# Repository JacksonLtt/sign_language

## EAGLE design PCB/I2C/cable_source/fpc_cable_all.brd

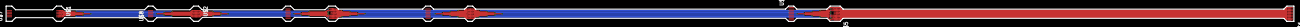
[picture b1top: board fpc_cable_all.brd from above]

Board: 2 copper layers, 422.3 x 5.0 mm, 11 parts (0 on the bottom side), 9 nets.

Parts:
U$1, U$2, U$7, U$8: FPC050505; FPC0505
U$3, U$4, U$9, U$10: FPC070505; FPC0705
U$5, U$6, U$11: FPC090505; FPC0905

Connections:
1.8V: U$1.P$4, U$2.P$4, U$3.P$5, U$4.P$5, U$5.P$6, U$6.P$6
GND: U$1.P$1, U$2.P$1, U$3.P$2, U$4.P$2, U$5.P$3, U$6.P$3
SCL1: U$5.P$4, U$6.P$4
SCL2: U$3.P$3, U$4.P$3, U$5.P$2, U$6.P$2
SCL3: U$1.P$2, U$2.P$2, U$3.P$1, U$4.P$1, U$5.P$1, U$6.P$1
SDA1: U$5.P$5, U$6.P$5
SDA2: U$3.P$4, U$4.P$4, U$5.P$8, U$6.P$8
SDA3: U$1.P$3, U$2.P$3, U$3.P$7, U$4.P$7, U$5.P$9, U$6.P$9
VIN: U$1.P$5, U$2.P$5, U$3.P$6, U$4.P$6, U$5.P$7, U$6.P$7

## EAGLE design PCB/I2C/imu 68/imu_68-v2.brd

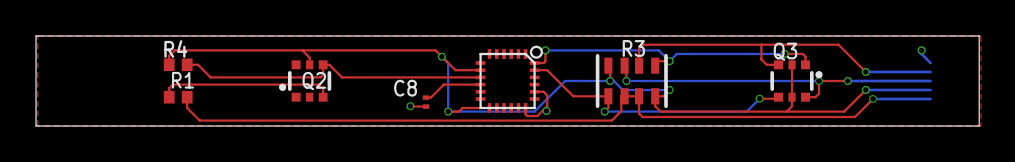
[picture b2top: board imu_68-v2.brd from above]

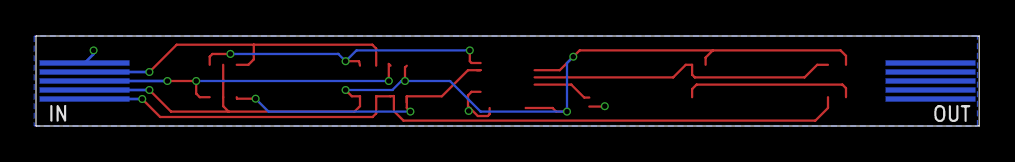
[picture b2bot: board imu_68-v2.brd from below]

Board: 2 copper layers, 52.4 x 5.0 mm, 9 parts (2 on the bottom side), 9 nets.

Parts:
C8: 0.1uF; C0201
Q2, Q3: BSS138; SOT363
R1, R4: 4.7k; R0402
R3: 10K; RESPACK_4X0603
U$1, U$2: FPC0510
U$21: MPU-9250_ICM20948; QFN24_3MM_NOEP

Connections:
1.8V: Q2.5, Q3.2, Q3.5, R3.4, R3.8, R4.2, U$1.P$2, U$21.8, U$21.13
GND: C8.2, Q2.3, R1.1, U$1.P$5, U$21.18, U$21.20
REGOUT: C8.1, U$21.10
SCK/SCL: Q3.3, R3.6, U$1.P$4
SCK/SCL_1.8V: Q3.4, R3.1, U$21.23
SDI/SDA: Q3.6, R3.7, U$1.P$3
SDI/SDA_1.8V: Q3.1, R3.5, U$21.24
SDO/ADR_1.8V: Q2.4, R4.1, U$21.9
VIN: R1.2, R3.2, R3.3, U$1.P$1

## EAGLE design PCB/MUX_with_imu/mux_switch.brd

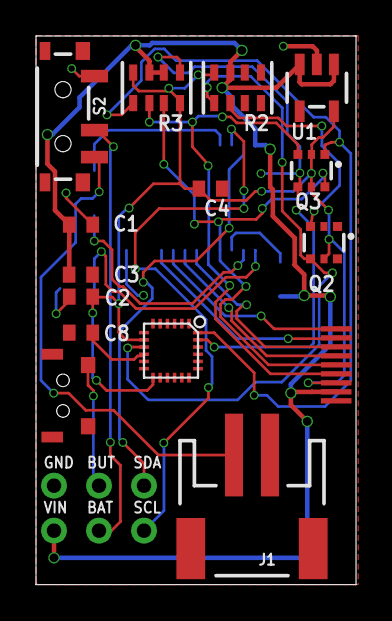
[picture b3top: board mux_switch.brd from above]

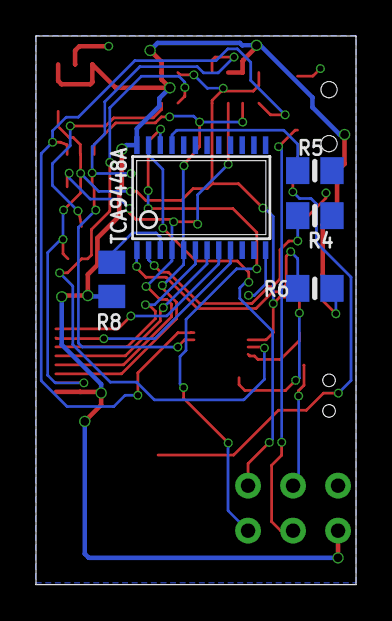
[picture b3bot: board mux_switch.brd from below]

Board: 2 copper layers, 17.8 x 30.5 mm, 26 parts (5 on the bottom side), 23 nets.

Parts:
C1: 1uF; C0402
C2: 2.2uF; C0402
C3: 10uF; C0402
C4, C8: 0.1uF; C0402
J1: JST-2-SMD
Q2, Q3: BSS138; SOT363
R2: 4.7K; RESPACK_4X0603
R3: 10K; RESPACK_4X0603
R4, R5, R6: 10K; 0805-NO
R8: 10k; R0805
S2: SWITCH_SPST_SMD_A
TCA9448A: MICROBUILDER_TSSOP24
U1: MIC5225-1.8V; SOT23-5
U$2: 24*3.5; 2*4*3.5
U$3, U$6, U$8, U$9, U$10, U$12: M0.9-HOLE0.9MM; M0.9-HOLE
U$13: FPC090505; FPC0905
U$21: MPU-9250_ICM20948; QFN24_3MM_NOEP

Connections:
1.8V: C2.1, C4.1, Q2.5, Q3.2, Q3.5, R2.8, R3.4, R3.8, U1.5, U$13.P$7, U$21.8, U$21.13
BATTERY: S2.2, U$10.P$1
BUTTON: U$2.P$4, U$9.P$1
GND: C1.2, C2.2, C3.2, C4.2, C8.2, J1.1, R4.2, R5.2, R6.2, S2.3, TCA9448A.12, U1.2, U$2.P$3, U$8.P$1, U$13.P$9, U$21.18, U$21.20
unnamed: R5.1, TCA9448A.21
unnamed: J1.2, S2.1
unnamed: R4.1, TCA9448A.2
unnamed: R6.1, TCA9448A.1
REGOUT: C8.1, U$21.10
RESET: R8.1, TCA9448A.3
SCK/SCL_1.8V: Q3.4, R3.1, U$21.23
SCL: TCA9448A.22, U$12.P$1
SCL1: Q3.3, R3.6, TCA9448A.5, U$13.P$6
SCL2: TCA9448A.7, U$13.P$4
SCL3: TCA9448A.9, U$13.P$2
SDA: TCA9448A.23, U$6.P$1
SDA1: Q3.6, R3.7, TCA9448A.4, U$13.P$5
SDA2: TCA9448A.6, U$13.P$3
SDA3: TCA9448A.8, U$13.P$1
SDI/SDA_1.8V: Q3.1, R3.5, U$21.24
SDO/ADR: Q2.3, R2.2
SDO/ADR_1.8V: Q2.4, R2.1, U$21.9
VIN: C1.1, C3.1, R2.7, R3.2, R3.3, R8.2, TCA9448A.24, U1.1, U1.3, U$3.P$1, U$13.P$8

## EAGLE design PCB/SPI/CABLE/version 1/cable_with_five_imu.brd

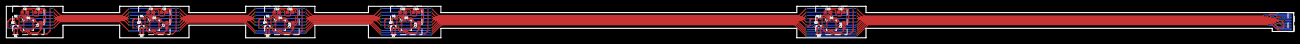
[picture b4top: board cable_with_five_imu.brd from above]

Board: 2 copper layers, 408.8 x 10.0 mm, 36 parts (1 on the bottom side), 21 nets.

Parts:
C4, C5, C7, C8, C10, C11, C13, C14, C16, C17: 0.1uF; 0603
C6, C9, C12, C15, C18: 1.0uF; 0603
Q1, Q3, Q4, Q5, Q6: 20V/0.2A/8MHz/1.2Ω/1Vth; SOT-416FL
R1, R2, R3, R4, R5, R6, R7, R8, R9, R12: 2.2k; 0402-TIGHT
U1, U3, U4, U5, U6: 9DoF IMU; QFN24-3X3
U$1: FPC1105

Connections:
1.8V: C5.1, C6.1, C8.1, C9.1, C11.1, C12.1, C14.1, C15.1, C17.1, C18.1, Q1.1, Q3.1, Q4.1, Q5.1, Q6.1, R1.2, R3.2, R5.2, R7.2, R9.2, U1.8, U1.13, U3.8, U3.13, U4.8, U4.13, U5.8, U5.13, U6.8, U6.13, U$1.P$5
!CS1: Q6.2, R9.1, U6.22
!CS2: Q5.2, R7.1, U5.22
!CS3: Q4.2, R5.1, U4.22
!CS4: Q3.2, R3.1, U3.22
!CS5: Q1.2, R1.1, U1.22
!CS!_VIN1: Q6.3, R12.1, U$1.P$8
!CS!_VIN2: Q5.3, R8.1, U$1.P$7
!CS!_VIN3: Q4.3, R6.1, U$1.P$6
!CS!_VIN4: Q3.3, R4.1, U$1.P$11
!CS!_VIN5: Q1.3, R2.1, U$1.P$10
GND: C4.2, C5.2, C6.2, C7.2, C8.2, C9.2, C10.2, C11.2, C12.2, C13.2, C14.2, C15.2, C16.2, C17.2, C18.2, U1.18, U1.20, U3.18, U3.20, U4.18, U4.20, U5.18, U5.20, U6.18, U6.20, U$1.P$1
MISO_VIN: U1.9, U3.9, U4.9, U5.9, U6.9, U$1.P$2
MOSI_VIN: U1.24, U3.24, U4.24, U5.24, U6.24, U$1.P$4
unnamed: C4.1, U1.10
unnamed: C7.1, U3.10
unnamed: C10.1, U4.10
unnamed: C13.1, U5.10
unnamed: C16.1, U6.10
SCLK_VIN: U1.23, U3.23, U4.23, U5.23, U6.23, U$1.P$3
VIN: R2.2, R4.2, R6.2, R8.2, R12.2, U$1.P$9

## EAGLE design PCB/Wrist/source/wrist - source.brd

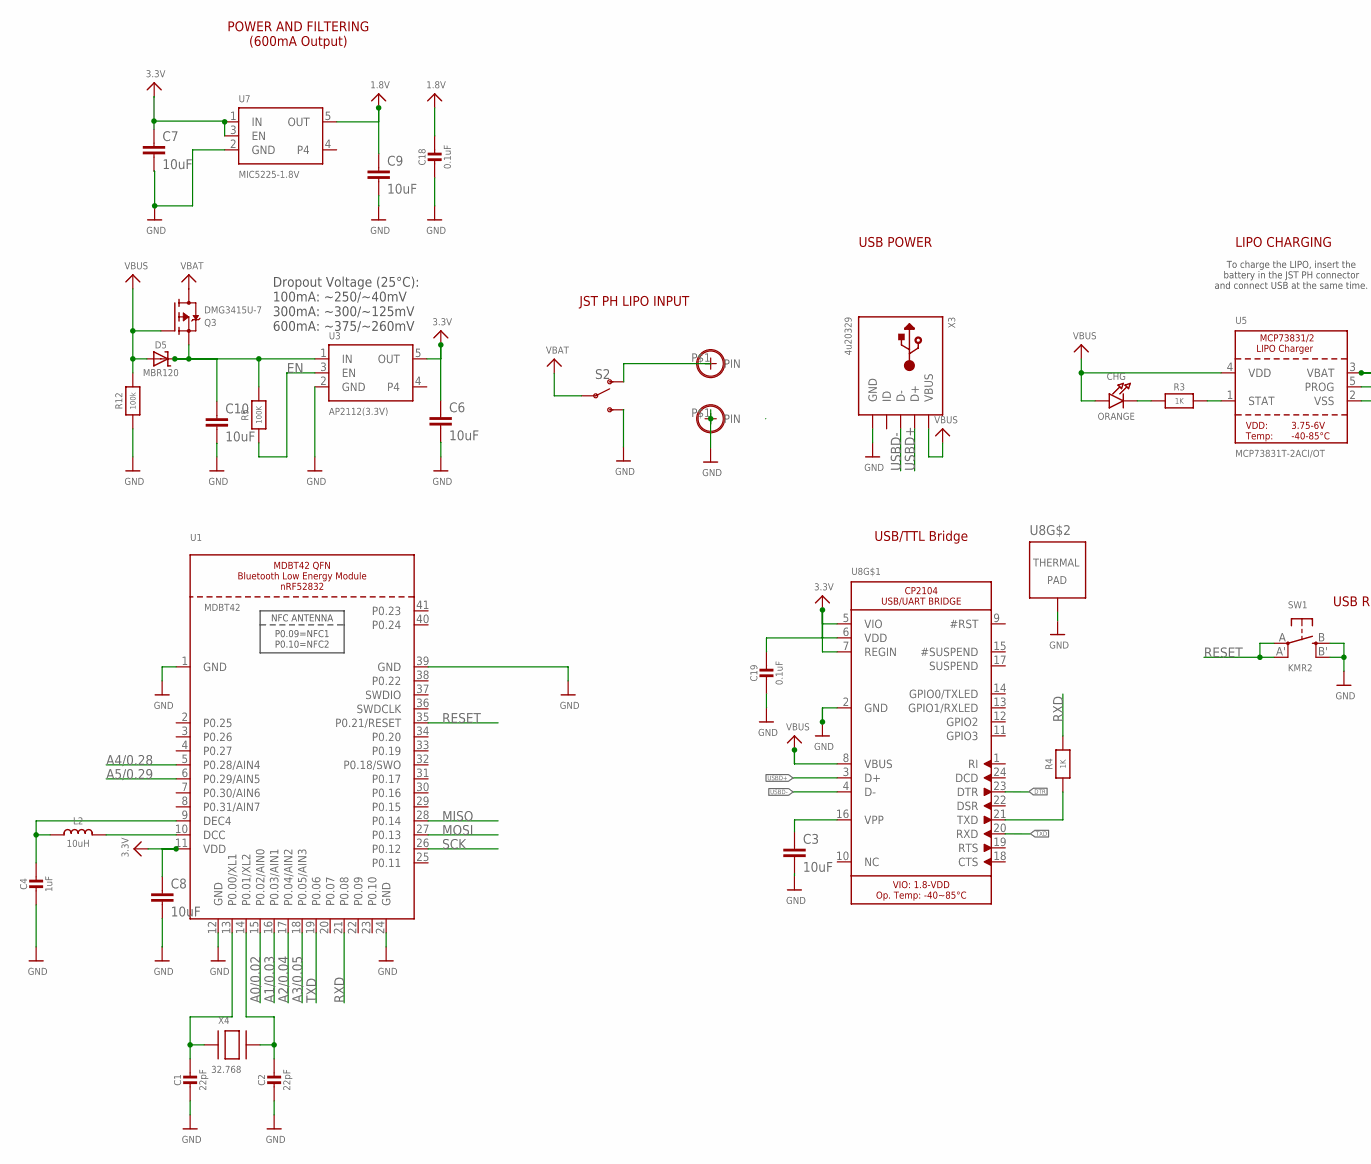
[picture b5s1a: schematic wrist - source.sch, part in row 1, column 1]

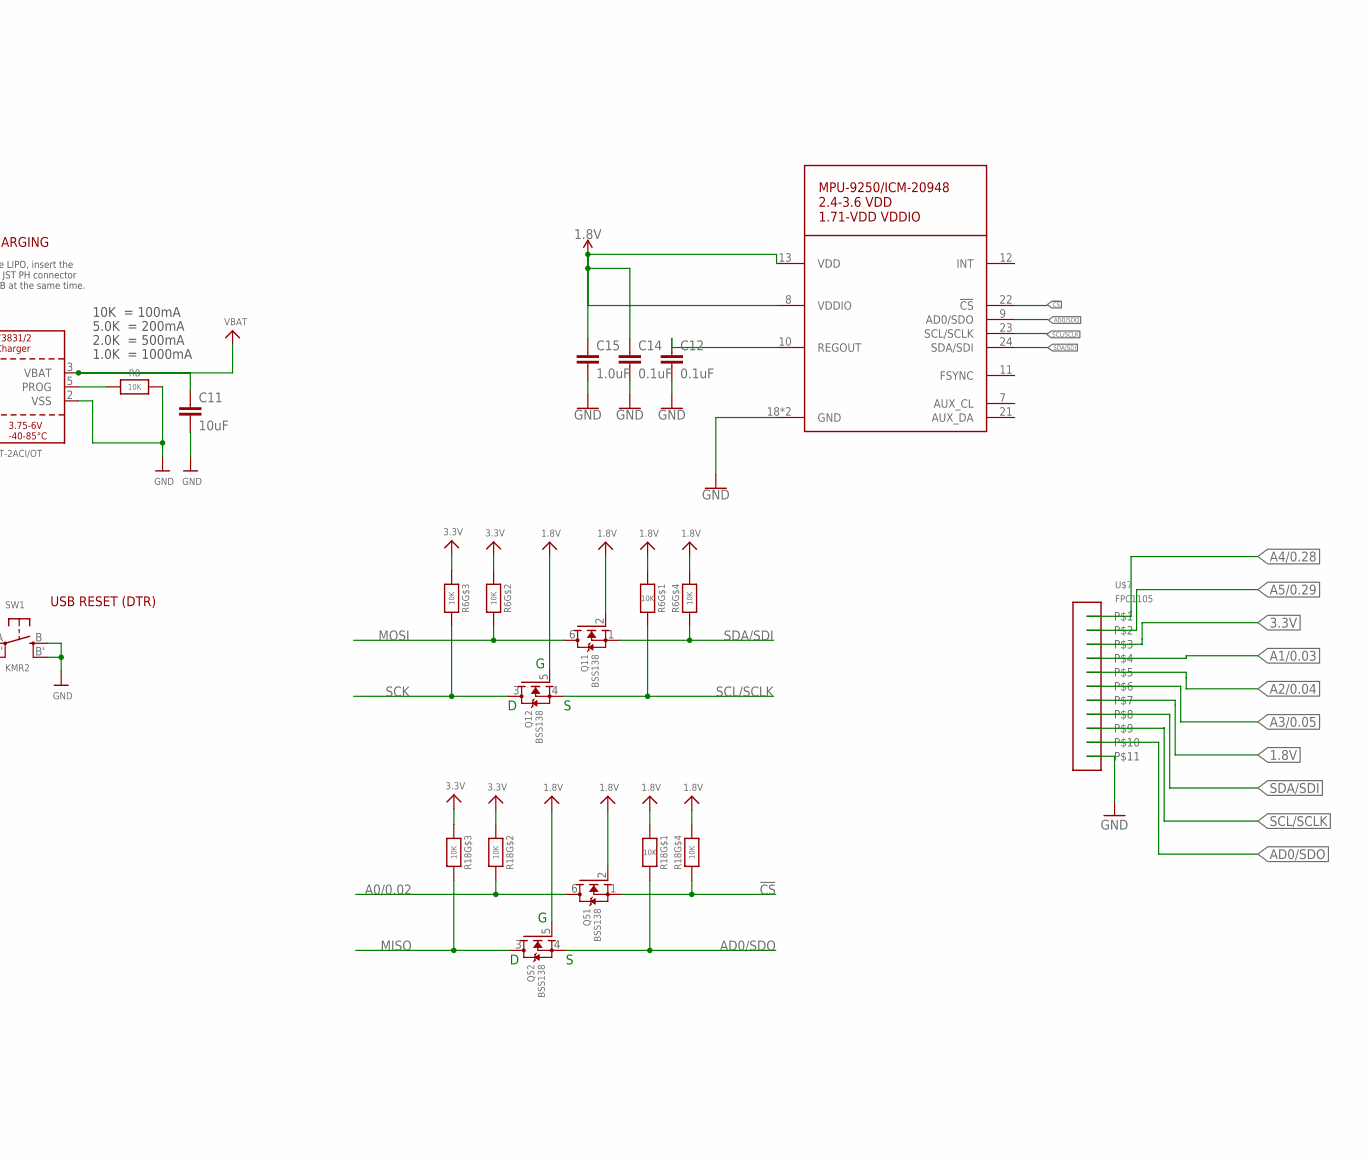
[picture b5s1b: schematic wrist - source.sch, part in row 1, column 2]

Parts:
C1, C2: 22pF; 0603-NO
C3, C6, C7, C8, C9, C10, C11: 10uF; C0603
C4: 1uF; 0603-NO
C12, C14: 0.1uF; 0603
C15: 1.0uF; 0603
C18, C19: 0.1uF; 0603-NO
CHG: ORANGE; CHIPLED_0805_NOOUTLINE
D5: MBR120; SOD-123
IC1: ADAFRUIT_SENSOR_MPU-9250_ICM20948; ADAFRUIT_SENSOR_QFN24_3MM_NOEP
L2: 10uH; 0805-NO
Q1, Q5: BSS138; SOT363
Q3: DMG3415U-7; SOT23-R
R3, R4: 1K; 0603-NO
R5: 100K; 0603-NO
R6, R18: 10K; RESPACK_4X0603
R8: 10K; 0603-NO
R12: 100k; 0603-NO
S2: SWITCH-SPDT-SMD-RIGHT-ANGLE; SWITCH_SPST_SMD_A
SW1: KMR2; BTN_KMR2_4.6X2.8
U1: MDBT42; BLE_MODULE_RAYTAC_MDBT42
U3: AP2112(3.3V); SOT23-5
U5: MCP73831T-2ACI/OT; SOT23-5
U7: MIC5225-1.8V; SOT23-5
U8: MICROBUILDER_CP2104; MICROBUILDER_QFN24_4MM_SMSC
U$7: FPC1105
U$9, U$13: M3-HOLE_M0.9-HOLE0.9MM; M3-HOLE_M0.9-HOLE
X3: 4u20329; 4UCONN_20329_V2
X4: 32.768; XTAL3215

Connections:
1.8V: C9.1, C14.1, C15.1, C18.1, IC1.8 (VDDIO), IC1.13 (VDD), Q1.2 (G), Q1.5 (G), Q5.2 (G), Q5.5 (G), R6.4 (1), R6.8 (2), R18.4 (1), R18.8 (2), U7.5 (OUT), U$7.P$7
3.3V: C6.1, C7.1, C8.1, C19.1, R6.2 (1), R6.3 (1), R18.2 (1), R18.3 (1), U1.11 (VDD), U3.5 (OUT), U7.1 (IN), U7.3 (EN), U8.5 (VIO), U8.6 (VDD), U8.7 (REGIN), U$7.P$3
!CS: IC1.22 (!CS), Q5.1 (S), R18.5 (2)
A0/0.02: Q5.6 (D), R18.7 (2), U1.15 (P0.02/AIN0)
A1/0.03: U1.16 (P0.03/AIN1), U$7.P$4
A2/0.04: U1.17 (P0.04/AIN2), U$7.P$5
A3/0.05: U1.18 (P0.05/AIN3), U$7.P$6
A4/0.28: U1.5 (P0.28/AIN4), U$7.P$1
A5/0.29: U1.6 (P0.29/AIN5), U$7.P$2
AD0/SDO: IC1.9 (AD0/SDO), Q5.4 (S), R18.1, U$7.P$10
DTR: U8.23 (DTR)
EN: R5.1, U3.3 (EN)
GND: C1.2, C2.2, C3.2, C4.2, C6.2, C7.2, C8.2, C9.2, C10.2, C11.2, C12.2, C14.2, C15.2, C18.2, C19.2, IC1.18 (GND), IC1.20 (GND), R8.2, R12.1, S2.3 (S), SW1.B (S), SW1.B' (S1), U1.1 (GND), U1.12 (GND), U1.24 (GND), U1.39 (GND), U3.2 (GND), U5.2 (VSS), U7.2 (GND), U8.2 (GND), U8.THERM (TP), U$7.P$11, U$13.P$1, X3.BASE@1 (GND), X3.BASE@2 (GND), X3.GND, X3.SPRT@1 (GND), X3.SPRT@2 (GND), X3.SPRT@3 (GND), X3.SPRT@4 (GND)
MISO: Q5.3 (D), R18.6 (2), U1.28 (P0.14)
MOSI: Q1.6 (D), R6.7 (2), U1.27 (P0.13)
unnamed: C1.1, U1.13 (P0.00/XL1), X4.P$1
unnamed: C2.1, U1.14 (P0.01/XL2), X4.P$2
unnamed: L2.2, U1.10 (DCC)
unnamed: CHG.C, R3.1
unnamed: C3.1, U8.16 (VPP)
unnamed: C12.1, IC1.10 (REGOUT)
unnamed: C4.1, L2.1, U1.9 (DEC4)
unnamed: R3.2, U5.1 (STAT)
unnamed: R8.1, U5.5 (PROG)
unnamed: S2.1 (O), U$9.P$1
unnamed: R4.1, U8.21 (TXD)
RESET: SW1.A, SW1.A' (P1), U1.35 (P0.21/RESET)
RXD: R4.2, U1.21 (P0.08)
SCK: Q1.3 (D), R6.6 (2), U1.26 (P0.12)
SCL/SCLK: IC1.23 (SCL/SCLK), Q1.4 (S), R6.1, U$7.P$9
SDA/SDI: IC1.24 (SDA/SDI), Q1.1 (S), R6.5 (2), U$7.P$8
TXD: U1.19 (P0.06), U8.20 (RXD)
USBD+: U8.3 (D+), X3.D+
USBD-: U8.4 (D-), X3.D-
VBAT: C11.1, Q3.3 (D), S2.2, U5.3 (VBAT)
VBUS: CHG.A, D5.A, Q3.1 (G), R12.2, U5.4 (VDD), U8.8 (VBUS), X3.VBUS
VIN: C10.1, D5.C, Q3.2 (S), R5.2, U3.1 (IN)

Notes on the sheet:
USB/TTL Bridge
USB RESET (DTR)
USB POWER
POWER AND FILTERING (600mA Output)
Dropout Voltage (25°C): 100mA: ~250/~40mV 300mA: ~300/~125mV 600mA: ~375/~260mV
10K = 100mA
5.0K = 200mA
2.0K = 500mA
1.0K = 1000mA
LIPO CHARGING
To charge the LIPO, insert the battery in the JST PH connector and connect USB at the same time.
JST PH LIPO INPUT

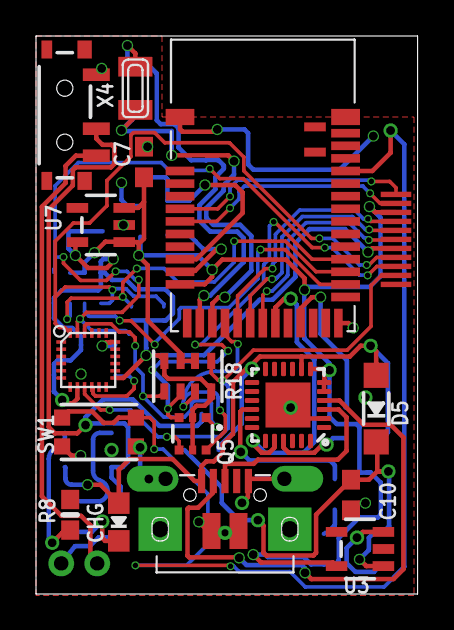
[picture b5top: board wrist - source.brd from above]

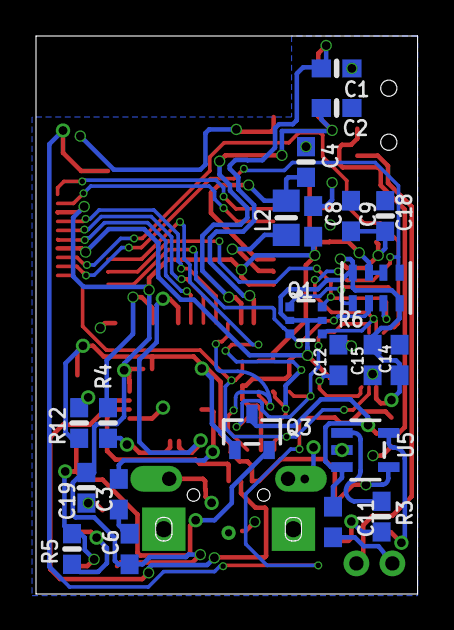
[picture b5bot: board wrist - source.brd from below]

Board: 2 copper layers, 21.2 x 31.0 mm, 41 parts (24 on the bottom side), 36 nets.

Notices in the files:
parts and their libraries:
microbuilder: This work is placed in the public domain, and may be freely used for commercial and non-commercial work with the following conditions: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
SparkFun-Connectors: Licensing: Creative Commons ShareAlike 4.0 International - https://creativecommons.org/licenses/by-sa/4.0
